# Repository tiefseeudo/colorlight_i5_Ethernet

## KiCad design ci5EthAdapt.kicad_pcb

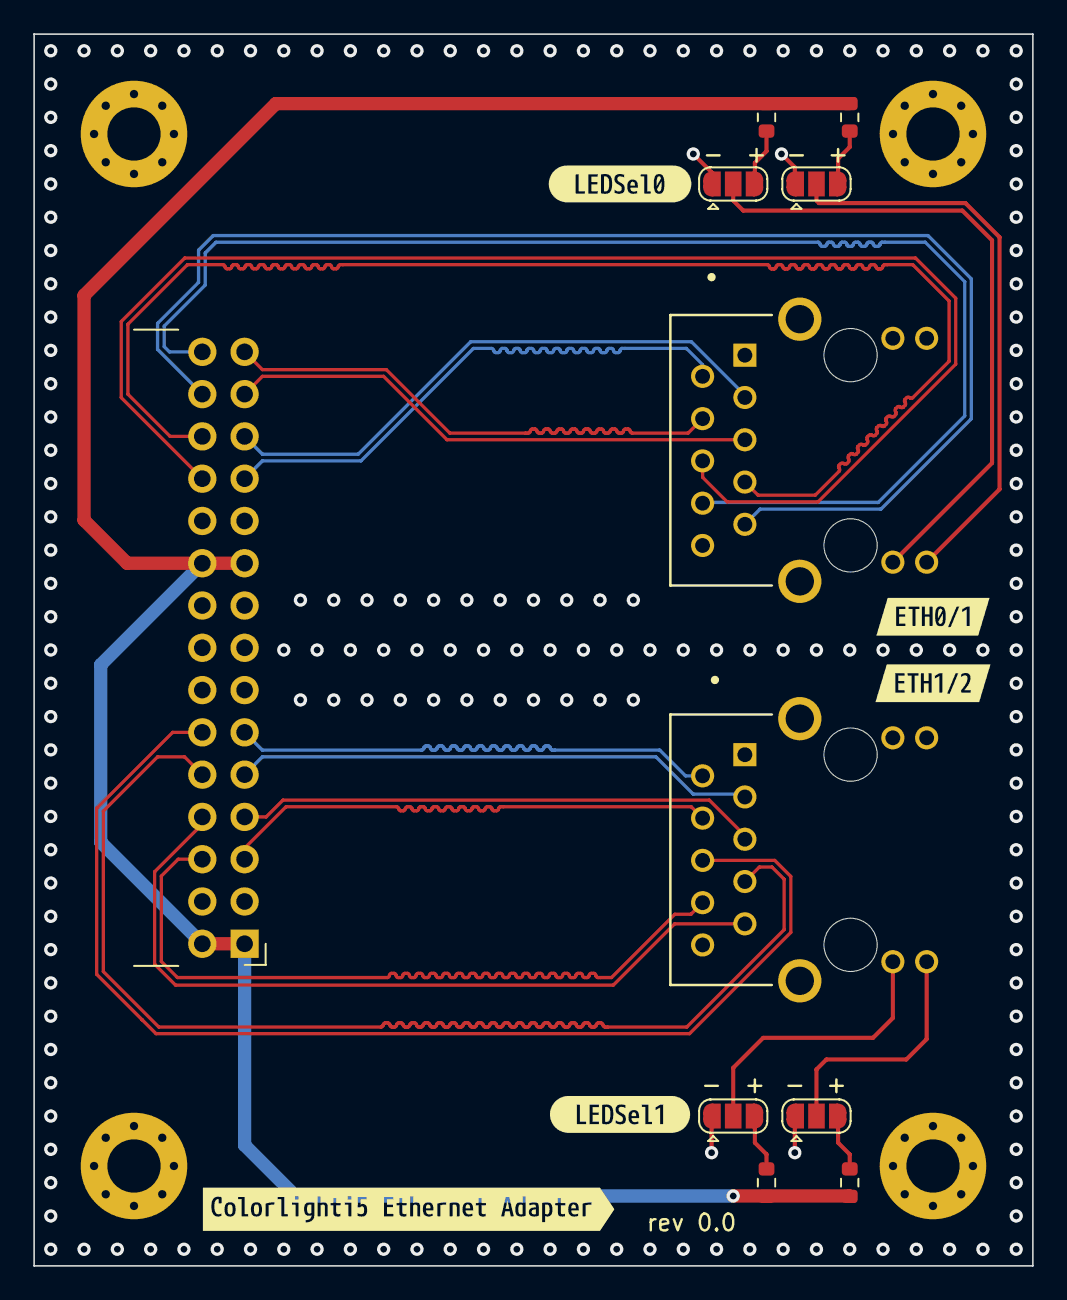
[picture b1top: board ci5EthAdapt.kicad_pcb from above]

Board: 4 copper layers, 60.0 x 74.0 mm, 20 parts (0 on the bottom side), 26 nets.

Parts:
H1, H2, H3, H4: M1; MountingHole_3.2mm_M3_Pad_Via
J1: Dual Pmod; PinHeader_2x15_P2.54mm_Horizontal
J2, J3: 74981104400; Wurth_Electronics-74981104400
JP1, JP2, JP3, JP4: LEDSel; SolderJumper-3_P1.3mm_Open_RoundedPad1.0x1.5mm
R1, R2, R3, R4: 1k; R_0603_1608Metric
kibuzzard-61D87B77: G***; kibuzzard-61D87B77
kibuzzard-61D87B97: G***; kibuzzard-61D87B97
kibuzzard-61D87CE6: G***; kibuzzard-61D87CE6
kibuzzard-61D87CF3: G***; kibuzzard-61D87CF3
kibuzzard-61D87D9F: G***; kibuzzard-61D87D9F

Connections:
+3V3: J1.1, J1.2, J1.19, J1.20, R1.2, R2.2, R3.2, R4.2
/ConnectorRJ45_ETH0/AnodeGreen0: J2.13 (CathodeY-AnodeG), JP1.2 (C)
/ConnectorRJ45_ETH0/CathodeGreen0: J2.14 (AnodeY-CathodeG), JP2.2 (C)
/ConnectorRJ45_ETH1/AnodeGreen0: J3.13 (CathodeY-AnodeG), JP3.2 (C)
/ConnectorRJ45_ETH1/CathodeGreen0: J3.14 (AnodeY-CathodeG), JP4.2 (C)
/ETH0.TRD_0N: J1.25, J2.3 (D1-)
/ETH0.TRD_0P: J1.23, J2.2 (D1+)
/ETH0.TRD_1N: J1.27, J2.5 (D2-)
/ETH0.TRD_1P: J1.29, J2.4 (D2+)
/ETH0.TRD_2N: J1.26, J2.7 (D3-)
/ETH0.TRD_2P: J1.24, J2.6 (D3+)
/ETH0.TRD_3N: J1.28, J2.9 (D4-)
/ETH0.TRD_3P: J1.30, J2.8 (D4+)
/ETH1.TRD_0N: J1.9, J3.3 (D1-)
/ETH1.TRD_0P: J1.11, J3.2 (D1+)
/ETH1.TRD_1N: J1.7, J3.5 (D2-)
/ETH1.TRD_1P: J1.5, J3.4 (D2+)
/ETH1.TRD_2N: J1.10, J3.7 (D3-)
/ETH1.TRD_2P: J1.12, J3.6 (D3+)
/ETH1.TRD_3N: J1.8, J3.9 (D4-)
/ETH1.TRD_3P: J1.6, J3.8 (D4+)
GND: H1.1, H2.1, H3.1, H4.1, J1.3, J1.4, J1.16, J1.21, J1.22, J2.10 (GND), J3.10 (GND), JP1.1 (A), JP2.1 (A), JP3.1 (A), JP4.1 (A)
unnamed: JP1.3 (B), R1.1
unnamed: JP2.3 (B), R2.1
unnamed: JP3.3 (B), R3.1
unnamed: JP4.3 (B), R4.1

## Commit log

2022-01-29 initial commit, rev0.0
